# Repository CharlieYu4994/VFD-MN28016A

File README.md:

# VFD-MN28016A
虽然大概率能用，但是请小心行事（（（

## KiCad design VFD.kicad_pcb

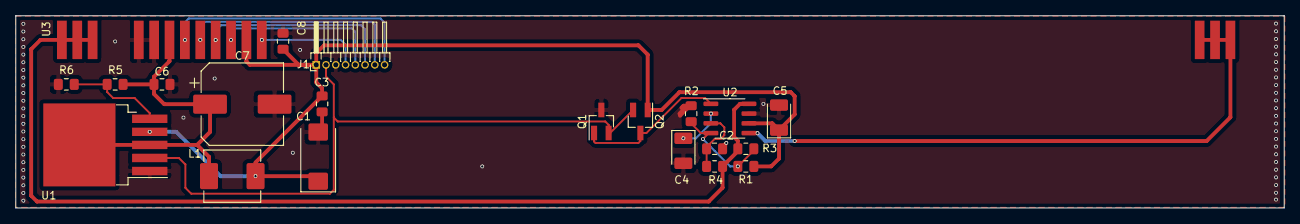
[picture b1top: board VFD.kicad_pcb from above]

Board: 2 copper layers, 165.0 x 25.0 mm, 21 parts (0 on the bottom side), 16 nets.

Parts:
C1: 220uF; CP_EIA-7343-15_Kemet-W_Pad2.25x2.55mm_HandSolder
C2: 102; C_0805_2012Metric_Pad1.18x1.45mm_HandSolder
C3, C6: 105; C_0805_2012Metric_Pad1.18x1.45mm_HandSolder
C4: 1uf; CP_EIA-3528-12_Kemet-T_Pad1.50x2.35mm_HandSolder
C5: 10uf; CP_EIA-3528-12_Kemet-T_Pad1.50x2.35mm_HandSolder
C7: 220uF; CP_Elec_10x10.5
C8: 104; C_0805_2012Metric_Pad1.18x1.45mm_HandSolder
J1: Conn_01x08_Male; PinHeader_1x08_P1.27mm_Horizontal
L1: 47uH; L_Abracon_ASPI-0630LR
Q1: SI2306; SOT-23_Handsoldering
Q2: SI2305; SOT-23_Handsoldering
R1, R2, R3: 103; C_0805_2012Metric_Pad1.18x1.45mm_HandSolder
R4: 223; C_0805_2012Metric_Pad1.18x1.45mm_HandSolder
R5: 393; C_0805_2012Metric_Pad1.18x1.45mm_HandSolder
R6: 102; C_0805_2012Metric_Pad1.18x1.45mm_HandSolder
U1: XL6019E1; TO-263-5_TabPin3
U2: LM9022; SOIC-8_3.9x4.9mm_P1.27mm
U3: MN28016A

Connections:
+5V: C1.1, C3.1, C5.1, C8.1, J1.1, L1.1, Q2.1, R1.1, U1.4, U2.6, U3.9
/F1: R3.1, R4.2, U2.8, U3.1
/F2: U2.5, U3.11
EN: J1.2, Q1.2, Q2.2, U1.2
GND: C1.2, C2.2, C3.2, C4.2, C5.2, C6.2, C7.2, C8.2, J1.3, Q1.3, R2.1, R6.2, U1.1, U2.7, U3.2, U3.3
unnamed: C2.1, R4.1, U2.3
unnamed: C4.1, U2.2
unnamed: J1.4, U3.10
unnamed: J1.5, U3.8
unnamed: J1.6, U3.7
unnamed: J1.7, U3.6
unnamed: J1.8, U3.5
unnamed: Q1.1, Q2.3, U2.1
unnamed: R1.2, R2.2, R3.2, U2.4
unnamed: R5.2, R6.1, U1.5
Vdrive: C6.1, C7.1, L1.2, R5.1, U1.3, U3.4

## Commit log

2021-02-16 删除无用文件
